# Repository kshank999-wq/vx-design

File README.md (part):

# VX Design

Spec-driven electronics and hardware engineering platform: specification → plan →
sourced parts → power budget → KiCad board → manufacturing files → enclosure, with every
decision traced to evidence.

The master specification is [docs/SPEC.md](docs/SPEC.md) (v1.1). It merges the v0.1 platform spec and the
v1.0 product spec, and marks what is built. The source documents are in [docs/specs/](docs/specs/), and
[docs/ASSESSMENT.md](docs/ASSESSMENT.md) holds the feasibility assessment. Deployment (Vercel, Supabase, worker host):
[docs/DEPLOY.md](docs/DEPLOY.md).

## Layout

| Path | Purpose |
|---|---|
| `apps/web/` | Next.js interface and Vercel endpoints |
| `services/orchestrator/` | Worker lifecycle, planning, approvals, queue |
| `services/engineering/` | KiCad / CAD / simulation adapter workers |
| `packages/contracts/` | Typed task, artifact, evidence and decision schemas |
| `packages/integrations/` | Provider connectors and capability registry |
| `packages/planning/` | Spec ingestion (DOCX/PDF/Markdown), cited requirement extraction, plan generation and validation |
| `supabase/migrations/` | Postgres schema, RLS and policies |
| `supabase/seed.sql` | G0 capability matrix starting rows |
| `tests/fixtures/` | Small circuits, STEP models and golden outputs |
| `docs/` | Assessment, architecture decision records, runbooks |

## Getting started

Requires Node 22+ and pnpm.

```bash
pnpm install
pnpm typecheck
pnpm test
pnpm test:db   # applies migrations to a throwaway local Postgres and runs schema tests
pnpm dev       # web app on http://localhost:3000
```

G0 capability audit (needs Docker): `./scripts/g0-run.sh` builds the engineering worker image,
runs every tool spike and writes [docs/g0/capability-matrix.md](docs/g0/capability-matrix.md).

To connect a Supabase project, copy `.env.example` to `apps/web/.env.local` and fill in the
project URL and anon key, then apply `supabase/migrations/` (Supabase CLI: `supabase db push`).

## G1: specification to approved plan

1. **Upload** a DOCX, PDF, Markdown or text spec. It is parsed into sections and blocks with stable ids (`S2.1.p3`).
2. **Extract requirements.** Claude returns each requirement with a block id and a verbatim excerpt. Every
   excerpt is checked against the document; unverifiable ones get one correction round, then are dropped
   and reported. Codes (`REQ-PWR-002`) are assigned deterministically in document order.
3. **Review**: confirm or reject requirements; ambiguities and open questions are listed.
4. **Generate a plan.** Claude proposes a task graph; deterministic checks require valid keys, known
   dependencies, no cycles, an acceptance test per task, and every requirement covered or explicitly
   deferred (up to 2 repair rounds). High/critical-risk tasks always get an approval gate.
5. **Edit** tasks while the plan is a draft, **submit**, then an owner/reviewer **approves** (or returns it
   with a note). Approval freezes the baseline, supersedes the previous one and makes tasks runnable.
   Changes after that go through **Revise**, which creates a new draft version.

The database enforces the workflow (status changes only through `submit_plan` / `decide_plan` /
`revise_plan`; frozen task definitions; dependency order), covered by `supabase/tests/planning_test.sql`.

Run locally (needs Docker):

```bash
npx supabase start                 # local Postgres/Auth/Storage, applies migrations + seed
cp .env.example apps/web/.env.local   # fill in the local URL/anon key printed above
pnpm --filter @vx/web build && pnpm --filter @vx/web start
pnpm test:e2e                      # browser flow; run the app with VX_LLM=offline to avoid model calls
```

### Guided setup and the look of the app

**Guided setup** (`/projects/<id>/setup`, "Guided setup" on the project page) takes a new project through five steps,
one at a time:
1. **Project:** name, code and description, and the product class chosen from chips.
2. **Mock-up:** reference images, and a link to the concept rounds.
3. **Intake:** markets, power, radios and standards as chips, size as three boxes, and the feasibility check.
4. **Inputs:** specifications uploaded here; parts and prior work are counted.
5. **Review and plan:** what is still missing, then "Generate the plan".

A readiness ring shows how much of what the planner needs is filled in. A manifest and the project's recent activity
sit beside the steps.

**Screens, not long pages:**
- **Project page tabs:** Overview, Documents, Requirements, Plans and runs, Standards and Team (`?tab=`).
  - **Overview:** summary tiles, the Project inputs button and the grouped sections.
  - **Requirements:** 50 per page, with search and status and document filters.
  - **Documents:** the first 8 are shown, with a button for the rest.
- **Project inputs:** five screens (Specifications, Mock-ups, Parts chosen, Prior work, Plan) with the step list on the
  left, Back and Continue, and a summary of what the plan builds on (`?step=`). Forms return to the step they were sent
  from.
- **Long lists:** the earlier-work register's subsystem groups start closed when there are more than 30 items.
- **Plan page:** tasks are grouped by stage (S0–S8). A stage index at the top shows the task count and how many are
  done. Each stage is a collapsible section with its task count, hours, approval gates, high-risk tasks and, once
  approved, a progress bar.
- **Project menu:** on every project page (staff), under the header. It holds Overview, Inputs and Workspace, then
  Define, Design, Make and Prove as drop-downs, with the current page and its group highlighted.
- **Busy pages in tabs** (`SectionTabs`): one section at a time. The open tab comes from `?tab=`, else the last tab opened
  on that page in this browser session (so saving a form returns to it), else where the work is.
  - **Run:** report, tasks, activity. Approvals waiting stay above the tabs.
  - **RFQ:** manifest, files, suppliers, packet, emails, quotes. It opens at the current step.
  - **Flux report:** summary and findings, migration plan, current design, revisions, earlier decisions, files.
  - **Validation:** verification, units, test plan, faults, test runs.
  - **Manufacturing routes:** parts to make, add a part, export for 3D printing.
  - **Release:** readiness, files, issue (draft) or files, changes from the last revision, production lots (issued).
  - **Compliance:** items grouped as failed, open, passed and not applicable; suggestions from the intake; certified modules.
  - **Lifecycle:** watch, cases, cost history. A case is impact, substitutes, resolution, opening at its current step.
  - **Production lot:** units, inspections, disposition.
  - **Intake and risks:** intake, risk register (forms return to their tab).
  - If a tab empties after a form (its last suggestion added), the page shows where the work is.
- **Stages:** one line per stage with its task count and status; the current stage (and any reopened or signed off past
  open items) is expanded.
- **Folder uploads:** every upload box takes files, a whole folder (the "Choose a folder" button) or anything dragged onto
  it, sub-folders included. System clutter (.DS_Store, Thumbs.db, __MACOSX) is left out, and each box keeps only the
  file types it takes, saying how many it left out. Flux imports take whole export folders. When two files share a
  name, the sub-folder becomes part of the name.
- **Updating the plan:** the planner reads every input, including the parts chosen from their datasheets (PT-n, with
  their specifications and model files; every one must be used by a task or its replacement argued). When anything is
  added or changed after a plan is made, the project, Project inputs and plan pages list what is new. "Update plan vN
  with these changes" sends the current plan's tasks and only the new or changed inputs; the planner returns just the
  tasks to add, change or remove, which are merged and checked like a full plan (every requirement covered or deferred,
  every part addressed). The new version says what it changed. "Rebuild from scratch" plans everything again.
- **Plan being built:** a large card at the top of the project, Project inputs and plan pages shows what is happening
  (updating vN or building from scratch), a live clock and the steps, and warns when no worker has picked the request
  up after three minutes. The update buttons are hidden meanwhile.
- **AI usage:** every AI call (website and workers) is priced from one token price table (`packages/planning/src/llm/pricing.ts`)
  and recorded with its purpose, tokens, cache use, time and who asked (`record_ai_call`); calls that fail after the
  model ran are billed and marked. Each project has an **AI usage** page (menu): this month, all time, cost per minute
  of AI time, by activity, and every call. The Account page totals AI spend by month, project and activity.
- **Billing (groundwork):** Account → **Billing** shows the prepaid balance, the plan, card top-ups (Stripe Checkout)
  and a statement per month (page and CSV) listing every charge with the AI call behind it: project, activity, model,
  tokens, our cost and the amount charged. Plans on offer (placeholder prices in `account_plans`): **Pay as you go**
  (no fee, cost + 25%), **Studio** ($50/month, AI at exact cost), **Team** ($150/month including $100 of AI at cost).
  Every cost event in a billed account's projects is charged as it is recorded (`billing_ledger`); the plan fee once a
  calendar month. When the balance reaches zero, AI work pauses (running runs stop at their next checkpoint, plan
  builds and AI actions are refused before any call is made) until credit is added. The internal plans (`standard`,
  `unlimited`) are not billed and keep their monthly allowances. Estimates on billed plans include the markup.
- **Build vs buy** (Define → Build vs buy, and a link on the plan's selection tasks): describe a subsystem (kind,
  interfaces, radios, the supply rail, the space, the markets it must be certified for). Code checks every module in
  the modules catalog against it and says why each one does not fit, or which facts the catalog lacks (unknown, never
  assumed). **Find more modules with AI** asks the model for candidates; only part numbers a distributor (or the parts
  catalog) confirms are added, as draft catalog entries that say where they came from (the model's certification
  claims are kept as a note, not as certifications). **Compare** creates a trade study of up to four fitting modules
  against a custom (chip-down) design on the module-vs-custom criteria: catalog facts where known, stated rules of
  thumb (integration and design hours at $120/h, certification costs, weeks to prototype) where not, all editable;
  **Fill from catalog** adds current prices. A decided study is a decision the next plan update builds on (TS-n).
- **Where things stand, everywhere.** Under the project menu, every project page shows the design run live: what it
  is working on (with a running clock and its latest step), how many results wait for you, the AI spend, and a link
  back to the run; the menu has **Runs** (every run). The run page has a large live panel and **Raise budget** (a run
  stopped only by its budget continues). The Workspace opens with a step-by-step line (inputs, concept, plan, design
  run, your approvals, manufacturer package: done, working, or your turn) and its activity panel with the results
  waiting for approval, what is working now and the recent activity log. With stage gates off, the stage bar follows
  the work.
- **Overnight runs and continuing a run.** "Run straight through (overnight)" (when authorizing, on the run page, or
  when continuing) approves every result whose VX Design checks pass instead of stopping for it; each automatic
  approval is recorded with the reason it would have stopped, on the authority of whoever turned it on. Failed checks
  still stop that task while the rest carries on; releases are never issued automatically. A run that stopped for
  input continues as the same run (**Continue the run**), with a new budget, approving what passed when overnight is on.
- **Plain-language summaries and questions for you.** When a step finishes, a small, inexpensive model writes 2–4
  sentences in everyday language: what was done, what it means for the product, whether the checks passed. The
  summary is shown first on approval cards, finished checklist items, result tiles, the run page and the result page,
  with **See the full technical explanation** one click away. The same pass may raise up to three questions only the
  owner can decide (markets, budget, features), each with a recommendation. Runs never wait on a question: the work
  follows the recommendation until someone answers under **Questions for you** in the Workspace (a choice, their own
  words, the recommendation, or "Not relevant"), and every later step is given the answers. The live strip shows how
  many questions are open; **Questions** (project menu) lists them one card per question, grouped by the step that
  raised them, with the recommendation highlighted and "Accept all recommendations". Each question can be read aloud (🔊) and answered by
  dictation (🎤), using the browser's own speech features (dictation in Chrome, Edge and recent Safari). Cost: part of "Plain-language summaries" on the AI usage page.
- **Calculation checks have roles.** Each check in a calculation is a requirement (must pass), a stretch target
  (reported, does not block) or an information-only scenario (an alternative the design does not rely on, such as an
  oscillator without the compensation the design uses). A scenario counts as information only when a requirement
  check on the same requirement sits beside it, and a stretch check on a must requirement is a requirement, so a
  real shortfall still fails the step.
- **The look, always in view.** Concepts opens on a **Mock-ups** tab (the team's sketches, renders and photos, large)
  under a "What we are building" strip with the frozen design or first mock-up; **Design freeze** and **Generated
  concepts** are tabs beside it. Once a design is frozen, the worker describes its image in words once (a small
  model looking at it) and every later step's context carries the look: that description, the envelope, the finish
  and the list of mock-ups.
- **Import existing designs** (project menu: Design → Import existing designs; was "Flux import"). Each import records
  where the work comes from (KiCad, Eagle/Fusion, Altium, EasyEDA, PADS, CADSTAR, Allegro/OrCAD, Flux, SolidWorks,
  Fusion 360/Onshape/Creo/Inventor, or any other tool), and the page says what to export from each. Running it audits
  the exports as before (BOM, placement, netlists, Gerbers, revisions, earlier decisions) and also sends every native
  board file to the KiCad worker (`import_conversions`): KiCad's own importers convert Eagle, Altium, EasyEDA, PADS,
  CADSTAR, Allegro, P-CAD, Fabmaster and SolidWorks PCB boards to KiCad (`vx_eng import-board`), the design-rule check
  runs, and the board's size, layers, parts and nets are reported with the converted board to download. STEP, IGES and
  STL models are measured (`vx_eng model-facts`). Schematics stay in their original tool (KiCad converts boards only);
  IPC-2581 and ODB++ go through the manufacturing-export audit. SolidWorks' native files need a STEP export.
- **Prices and earnings.** Customers see one price per AI call (our cost times their plan's rate). Plans describe their
  price per million tokens, never the markup; statements, the CSV, the billing summary and the AI usage page carry no
  "our cost", and the database withholds the ledger's cost column and the plans' markup from customers. VX Design
  administrators (`platform_admins`, added by SQL) see our cost, price and markup everywhere, and **Admin → Earnings**:
  markup earned from customers per month, and what in-house (unbilled) projects would have earned at a reference
  markup they set there.
- **Resolving a stopped run.** "What you need to do" shows one card per problem: what went wrong in plain words and
  buttons to **Try again** (that step, and the run continues), **Give guidance** (a box opens under the card; "Save
  guidance and try again" or "Save guidance only"; earlier guidance is listed on the card), **Save for later** (the run
  leaves it alone; **Bring back** under "Saved for later"), and for critical-risk steps **Include it and continue**.
  One **Fix everything above and continue the run** button sits below, with the run's budget shown and changeable under
  Options (every button uses the run's own budget). Older runs say so and link to the latest. When a worker is stopped
  (an update or restart), it hands its steps straight back to the queue instead of letting them count as
  interruptions; steps already blocked by interruptions are put back when the run continues.
- **DigiKey through the website.** When DigiKey's firewall blocks a worker's own connection, set `VX_PARTS_RELAY_URL`
  (the website's `/api/sourcing/digikey`) and `VX_PARTS_RELAY_TOKEN` on the worker, and the same token plus
  `DIGIKEY_CLIENT_ID`/`DIGIKEY_CLIENT_SECRET` on the website: the worker's DigiKey lookups then go through the website. While the website is behind Vercel's own sign-in, also set
  `VX_PARTS_RELAY_BYPASS` on the worker to the project's Protection Bypass for Automation secret.
  Opening `/api/sourcing/digikey` in a browser shows whether DigiKey answers the website and whether its keys and token
  are set (no secrets shown).
- **Intake reflects the project.** Empty intake fields (markets, radios, power, standards, size, use) are filled from the
  owner's answers, the requirements, the design freeze and the description, with a note saying where they came from;
  saving keeps them.
- **Moving on past a step.** A step that could not finish can be **put on hold and moved on**: it counts as done
  without its result (recorded as a warning, audited), the steps after it run, and it is listed under "On hold" with
  **Do it now**. The parts lookup puts itself on hold when every parts service refuses (keys, approvals, plan limits),
  instead of retrying. A step that ran out of its own AI limit gets **Raise it and try again** (a per-step override; the
  approved plan is unchanged). Run pages and the status bar follow the run that is working; a stopped run whose work is
  running in another run says so and links to it. The run page refreshes every 20 seconds.
- **Run chat.** Beside "What you need to do" on a stopped run is a chat with the design agent. Each step listed
  there has **Give guidance**, which opens the chat on that step: what you write is saved with the step (audited) and
  its next attempt reads it as it reads a reviewer's notes. Questions without a step go to the agent as in the
  Workspace. Dictation and read-aloud work here too.
- **Parts services that refuse.** A parts service that rejects the key, has used up its plan, or answers with an
  anti-bot page is asked once per parts list and then skipped with the reason, instead of failing every line.
- **What you need to do.** A stopped run says in plain words what stopped it: steps that could not finish (and why),
  critical-risk steps outside the run (only the owner can include them), results waiting, open questions, and steps
  waiting on hardware. **Fix these and continue the run** retries the failed steps with a fresh retry allowance,
  includes critical-risk steps if the owner ticks it, and can raise the AI and compute budgets. AI answers that run
  past the output limit are retried once with the full 128K output and less reasoning effort; answer formats too large
  for the API's constrained decoding are retried with the format in the instructions and checked here.
- **Approvals for non-engineers.** Each result waiting for approval says in plain language what VX Design checked
  and whether it passed ("Passed: all 4 checks passed"), with the engineering details folded away. **Approve everything
  that passed** approves every waiting result whose checks all passed; anything with a failed check is held.
- **A mock-up is the concept.** On Concepts, a project mock-up (or render, sketch, photo, drawing) can be frozen as the
  industrial design directly, with its envelope, instead of generating concepts (`concept_from_reference`).
- **Cost before you click:** each button that starts AI work shows its likely cost and where the figure comes from:
  plan update and rebuild, plan from requirements, reading specifications (only the blocks rules cannot read are
  counted; "no AI cost" when rules read it all), reading datasheets, chat questions and model comparisons. Figures come
  from this project's recorded calls, else the account's other projects, else typical figures (`apps/web/lib/cost-estimate.ts`).
- **Reading model:** each project chooses the model that reads its specifications and part datasheets (Opus 5.5 by
  default, Sonnet 5.5 or Haiku 5.5): AI usage → "Choose or compare", or the link on the Specifications step. **Compare
  models** reads one specification again with the chosen models, saves nothing as requirements, and matches each
  result against the requirements already read from it (same source paragraph, same meaning): found, missed, extra,
  kind and priority differences, cost and time, with the lists to check. Comparison calls show as "Model comparison".
- **Requirements with less AI:** a block identical to one already read in another specification of the project (a
  new revision) reuses those requirements; a clear sentence with one shall/must/should is read by rules (kind from its
  words, an acceptance criterion from its figures, vague words and TBD marked ambiguous); every other block goes to the
  model, and only those blocks are sent. Nothing is skipped by guesswork: only sections about the document itself
  (revision history, glossary, references, overview). Each specification shows how many requirements came by rules,
  reused, or by AI.
- **Parts from data before AI:** each datasheet's part number is found without AI (a "Part number" or "Ordering code"
  label, or a code in the file or package name that the datasheet itself contains) and looked up in the saved parts
  catalog, then at the distributors configured on the web server (Nexar, DigiKey, Mouser). An exact match supplies the
  maker, description, specifications, package and lifecycle; only datasheets nothing matches are read by AI. The result
  says how many came from data and how many from AI, and each part notes where its specifications came from.
- **Part packages (ZIP):** a manufacturer's ZIP can be dropped on Parts chosen as it is: it is opened, and its datasheets
  and 3D models become part files, noted with the package they came from. A model with no part number inside goes with
  the part its own package describes. ZIPs added on another step are listed on Parts chosen with "Read them as parts".
- **Workspace activity panel:** the plan's tasks are grouped by stage, with done/total. Stages with open work start
  expanded.

**Look:** the clean light design is the template: a blue-grey background with a faint blueprint grid, white cards,
navy panel headers in the workspace, and the S0–S8 stage strip on the project page and the workspace. Dark mode follows
the system until someone picks one with the switch in the header. The logo and favicon come from
`VX Design Chrome Orbit Logo.png`. The setup's chips, readiness ring and cyan accents come from the dark-tech concept.

### Project inputs

**Project inputs** (`/projects/<id>/inputs`, linked first on the project page) is where everything a plan is built
from comes together, and where the plan is generated:

1. **Specifications.**
   - **Upload:** any number at once, one per board, for the enclosure, for the software. Each file goes from the
     browser to a staging folder and is then checked and parsed as before.
   - **Extract:** "Extract requirements from N documents" reads them at the same time, then stores the results one
     document after another, so requirement codes continue across documents.
   - **Duplicates:** requirements that say nearly the same thing in two documents (word overlap ≥ 75%) are listed for
     a person to merge or keep.
2. **Mock-ups and references (`REF-n`).**
   - **What they are:** how the product should look: sketches, renders, photos, dimensioned drawings.
   - **Each one has:** a kind, a title, a note on what it shows and what to keep, and a "use in the plan" switch.
   - **Files accepted:** PNG, JPEG, WebP, GIF and PDF, checked on their bytes. SVG is refused because it can carry
     script.
   - **Concepts:** image references can be given to a concept round. The image model gets them as reference images,
     and their notes go into the brief.
3. **Parts already chosen.** Upload the manufacturer datasheets (PDF, or Word/text) and 3D or CAD files (STEP, STL,
   IGES); nothing has to be typed (`@vx/planning` part-identify.ts).
   - **Datasheets:** each is read for the orderable part number, which is kept only if it appears in the datasheet (a
     listed variant that does is used instead). Also read: the manufacturer, what the part is, its subsystem and up to
     12 key specifications. The part is created, or filled in if already listed, with the file attached. Up to 8 are
     read per press.
   - **Models:** each is attached to the part whose number (or variant) is in its STEP header or product names, or in
     its file name. The longest match wins.
   - **Unplaced files:** a file that cannot be read or matched is listed with the reason, and a person picks the part
     or types the number.
   - **By hand:** a part can still be typed in, from a collapsed form.

   Parts someone has already picked (`public.project_parts`), grouped by subsystem:
   - **Each one has:** part number, manufacturer, what it is for, subsystem, how far it got (candidate, selected,
     designed in, laid out, verified, rejected) and a note. A part number is listed once, ignoring case and punctuation.
   - **Files:** datasheets, 3D models (STEP) and drawings are attached to the part. The kind is worked out from the
     file: STEP is a 3D model, PDF a datasheet.
4. **Prior work.**
   - **Flux audits (`PW-n`).** Finished Flux audits marked for the plan. The planner gets, for each: board size, layers
     and whether it is routed; parts grouped by part number and role; rails and connectors; earlier decisions and
     claimed validations, all marked unverified; open problems and suggested next steps.
   - **Files from other tools or engineers (`REF-n`, kind "Prior design").** A KiCad project, a schematic PDF, a BOM
     spreadsheet, design notes, with a note on where each came from.
   - **What was already done: the earlier-work register (`PR-n`).** "Build the list of earlier work" asks a worker to read
     every earlier design document in full: the documents inside the Flux imports, the prior-design files and the
     parts' datasheets. It lists each part and design decision by subsystem with how far it got (considered, selected,
     designed, laid out, verified, rejected, open), quoting the document it came from. Items not quoted word for word
     are dropped. Parts entered by the owner override what the documents say.
   - **Corrections:** people can correct an item's status, add a note or leave it out. Corrections are kept by item
     across rebuilds.
5. **Other inputs.** The intake, the design freeze, confirmed standards and knowledge sources are shown with links,
   and also go to the planner.
6. **The plan.** "What the planner reads" shows the exact context. "Generate plan from these inputs" builds the plan.
   - **Each task** states its basis: it **reuses** earlier work, **adapts** it, **replaces** it, or **starts fresh**,
     citing the inputs it builds on and saying what remains.
   - **Earlier work must be addressed:** every register item that is selected, designed, laid out or verified must be
     cited by some task. A plan that ignores one is sent back for repair.
   - **Replacing:** a task that replaces earlier work must give its concerns and suggest alternatives.
   - **Validation:** a task citing an input that does not exist, or reusing work without citing any, is sent back for
     repair. Imported work is never treated as verified, so reused work still gets acceptance tests that
     re-establish it.
   - **Display:** the plan page shows each task's basis (with the earlier-work items named, and concerns and
     alternatives for replacements) and the inputs the plan was built on.
   - **Kept through changes:** the basis and the input list are stored with the plan and survive revisions and changes
     made from the workspace chat.

**Large plans go to a worker.** Planning hundreds of requirements takes longer than the hosted web server's 5-minute
request limit. Above 80 active requirements (`VX_WEB_PLAN_MAX_REQUIREMENTS`), "Generate plan" records a plan request
(`public.request_plan`) holding everything the planner reads. A worker then generates the plan with no time limit
and stores it as a draft version, with the same checks as a plan made on the web. Project inputs and the project
page show the request's progress (they refresh themselves), then a link to the plan, or the reason it failed. Only
one plan request runs per project at a time. `services/orchestrator/test/plan-request.test.ts` covers this path.

`supabase/tests/inputs_test.sql` covers the database rules: who may add references, the folder they must be stored
in, duplicates, image-only concept references, and the plan's inputs and basis through revision.
`pnpm test:e2e:inputs` covers the browser flow.

## G2: worker backbone

Approved plans are executed by workers (`services/orchestrator`), separate long-running processes
that are never on Vercel. The web app only authorizes runs and shows their status. Once a run is
authorized, the browser can be closed.

- **Authorize a run** on the approved plan: supervision mode, AI and compute budgets (USD), allowed risk
  levels, retries per task, and optionally stop at the first failure. Pause, resume or cancel it from the
  run page.
- **Durable queue.** Workers claim ready tasks in plan order (`claim_next_task`, `SKIP LOCKED`). Each claim
  is a lease that the worker renews with heartbeats. If a worker stops heartbeating, any other worker
  reclaims its task (`reap_stale_executions`). A task that keeps crashing workers is blocked after three
  interruptions.
- **Checkpoints.** Each executor step's result is saved in the execution's checkpoint. A resumed attempt
  skips finished steps, so model calls are not repeated, and it does not count as a retry.
- **Fenced commits.** Every write names the execution, and the database accepts it only from the worker
  that still holds the lease. A worker that was frozen or partitioned cannot commit after another worker
  has taken over. A unique index also allows at most one committed version per artifact per task.
- **Locks.** A worker must hold the per-artifact write lock (`acquire_artifact_lock`) to register outputs.
- **Budgets.** Model tokens (priced in `services/orchestrator/src/pricing.ts`) and worker time are recorded
  in `cost_events`. Reaching a budget stops the run, and in-flight work yields at its next checkpoint.
- **Sign-off.** Outputs commit when checks pass, unless the plan's approval policy requires sign-off, a test
  needs human review, or a Guided run reaches a design task. Those outputs wait on the run page for
  approve or return-with-note.
- **Report.** When nothing more can run, the worker writes an in-app completion report. It covers outputs,
  checks, recoveries, open approvals, spend, and recommended next steps.

Executors so far:
- **Design briefs** cover architecture, components, thermal, mechanical and documentation tasks (power tasks
  use the power calculator; enclosure tasks the enclosure generator; both below). They are Claude-drafted and checked against the task's requirements and acceptance tests.
- **Simulation tasks** (engineering worker): the model writes the analysis as named quantities (each input with
  its source: requirement, datasheet, upstream task or stated assumption), checks against the requirements, and,
  when a circuit matters, a self-contained ngspice deck with `.meas` statements. Every number is computed by the
  built-in calculator and ngspice, not taken from the model; an analysis that does not compute goes back to the
  model, and a check that computes but fails fails the task with the numbers, for a person to decide. Decks are
  refused if they try anything outside the simulator (`.control`, shell, `.include`).
- **Verification tasks**, two kinds. Before manufacturing: a design review that gathers every upstream task's
  tool checks (ERC, DRC, parity, fit, sourcing, power, simulation; any failure fails the review), then has the
  model read each board's circuit against the requirements and list must-fix / should-fix findings; a person
  signs off every review, in every run mode. After manufacturing (a fab task upstream): a hardware test. Draft
  test procedures for its requirements are added to the Validation page and the task waits for built units; it
  passes once approved procedures have passing runs for all of them (Continue on the run page to check again).
- **Boards.** Schematic, layout and board-power tasks name their circuit board (`tasks.board`; plan fixes infer it
  from upstream work or the key, e.g. `tc-sch-io` → `tc`). A board's tasks build on each other: each schematic task
  starts from the board's design so far and must keep its parts, a board's power tree feeds its schematic, and a
  later layout task takes over the earlier board when the circuit has not changed since (no second layout). One
  manufacturing task packages every board (`fab.<board>/…`) and one sourcing task buys for all of them (refs
  `board/R1`).
- **Manufacturing tasks** by what they produce: fab outputs (Gerbers, pick-and-place, panels) make the fab packages
  (engineering worker); documents (bring-up checklists, factory tests, fixtures) are design briefs; the **RFQ package**
  gathers every committed manufacturing output upstream (each board's fab package, BOMs, CPL, drawings, board and
  enclosure models, test plans, service and compliance documents, reviews) into a **draft release**, with a brief for
  the quote request. A person checks its readiness, issues it on Releases and sends RFQs from the RFQ page.
- **Enclosure before the boards:** an enclosure task with no routed board upstream writes the envelope as a design
  record (sizes, stack-up, bays) for the board tasks to work to; plan fixes make a later enclosure task wait for each
  board's last layout, so the housing is built around the real boards.
- Schematic (G3), simulation, PCB layout (G4) and manufacturing (G4.5) tasks wait for the KiCad engineering worker.
- **No paying for loops.** Every repair loop (plans, briefs, circuits, layouts, power trees, enclosures,
  simulations, assembly instructions) stops early when a round reports exactly the same problems as the round
  before, or returns an output it already returned with the same problems; the reason is recorded. Each task also
  has its own AI spend cap per run (by discipline, e.g. $15 schematic, $20 layout, $6 simulation; a task's
  `cost_budget_usd` overrides it): at the cap the task fails, not retried, for a person to decide.
- **Unchanged work is reused across plan versions.** At approval every task gets a fingerprint over its definition,
  the exact text of its requirements, its board and basis, and its upstream tasks' fingerprints. A task identical to
  one finished in an earlier plan takes over its committed outputs and checks (labelled "Reused from vN … unchanged")
  instead of running; a change anywhere upstream reruns everything below it. Sourcing is reused for 7 days only.
  The plan page marks reused tasks; **Do again** runs a reused task, and the reused work after it, afresh.

```bash
pnpm worker                        # SUPABASE_URL, SUPABASE_SERVICE_ROLE_KEY, ANTHROPIC_API_KEY (or VX_LLM=offline)
pnpm test:worker                   # kills and freezes real worker processes against local Supabase
pnpm test:e2e:g2                   # browser: authorize, close, kill worker, resume, approve, continue, report
```

## G3: first circuit

Schematic tasks run on the **KiCad engineering worker** (`services/engineering/Dockerfile.worker`: KiCad 10 +
the orchestrator + `vx_eng`). Workers advertise the disciplines they can execute, so a worker without KiCad
never claims a schematic task. The run page says when no online worker can run a task. If nothing else can
progress, the run ends with a report saying what it is waiting for.

1. **Design.** Claude proposes a circuit: KiCad library symbols and footprints, nets written as `REF.PIN`, and
   for each part its MPN, manufacturer, datasheet URL and the ratings the design relies on.
2. **Check and repair** (up to 3 repair rounds). `vx_eng` checks the design against the installed KiCad
   libraries:
   - symbols and footprints exist, with close matches suggested when they don't;
   - every pin referenced exists, with the symbol's real pin list in the error;
   - every symbol pin has a pad on its footprint;
   - every pin is connected or explicitly marked unconnected.
   
   It then generates the native schematic and runs KiCad ERC. It also checks that KiCad's own netlist matches
   the design. Every problem goes back to Claude with those library facts.
3. **Component evidence.** Each datasheet is downloaded, and the part number and every claimed rating are
   looked for in its text, with excerpts kept. This is a text match, and the UI says so.
4. **Outputs** (all deterministic, so a resumed task re-uploads identical files):
   - an editable KiCad 10 project (zip);
   - schematic SVG and PDF;
   - the ERC report (JSON);
   - the netlist;
   - a BOM (CSV);
   - the component evidence;
   - the design (JSON).
   
   The web app shows the drawing, the ERC table and the evidence table.

```bash
./services/engineering/build.sh                                        # KiCad engineering image (G0)
docker build -f services/engineering/Dockerfile.worker -t vx-engineering-worker .
pnpm test:eng                       # vx_eng: library checks, deterministic build, ERC negative controls
pnpm test:g3                        # worker routing, schematic build, the stored project re-checked in a fresh KiCad
pnpm test:e2e:g3                    # browser: waits for a KiCad worker, drawing, ERC report, evidence, approve
```

## G4: first board

PCB layout tasks also run on the KiCad engineering worker. They take the **committed circuit design** of their
upstream schematic task, so the schematic must be approved first.

1. **Placement.** Claude proposes:
   - the outline, corner radius and mounting holes (M2, M2.5 or M3);
   - a fab design-rule profile (`jlcpcb-2layer-standard`, `oshpark-2layer`, or `jlcpcb-4layer-standard` for dense
     boards with modules, fine-pitch connectors or more than about 40 parts);
   - a ground pour net, and on 4 layers the inner plane nets (In1 ground, In2 the main supply by default). The planes
     go in before routing, so the router drops those nets to them with vias and routes only signals on the outer
     layers. The fab package checks both inner layers are in the Gerbers and the fab notes give the stackup. When two
     layers leave ten or more connections unrouted, the repair message tells the model to switch to four;
   - a position, rotation and side for every component.
   
   It is given each footprint's courtyard extents from the KiCad library.
2. **Check and repair** (up to 3 repair rounds). Each problem goes back to Claude with exact geometry:
   - `vx_eng` checks the placement with KiCad's own footprints: courtyards must be inside the outline and must
     not overlap on the same side. Through-hole parts and holes block both sides. Problems give the allowed
     position range or the overlap size.
   - It builds a native `.kicad_pcb` linked to the schematic: footprints carry the symbol UUIDs and fields, and
     pads carry KiCad's net names.
   - **Freerouting** routes it. Supply nets get the wider "Power" net class. A ground pour is added on both
     layers.
   - **KiCad DRC** runs with `--schematic-parity` and zone refill. Pads whose thermal spokes can't all reach
     the pour get a solid connection, and DRC runs again.
   - Unrouted connections, DRC errors and parity differences go back to Claude.
3. **3D.** The KiCad library model of each footprint comes from
   [kicad-packages3D](https://gitlab.com/kicad/libraries/kicad-packages3D) at the KiCad version's tag. Models
   are fetched once and cached (`VX_3DMODEL_CACHE`). These are generic package shapes, not manufacturer CAD,
   and the model report says so.
4. **Outputs** (12 per task):
   - the KiCad 10 project (schematic + routed board);
   - 3D renders (iso, top, bottom);
   - copper/silk drawings (SVG, PDF);
   - board STEP and GLB;
   - the DRC report;
   - the 3D model report;
   - the placement.
   
   Routing is not bit-for-bit reproducible, so the files that passed DRC are stashed in storage in the same
   checkpointed step. A resumed task registers those exact files instead of routing again.

The web app shows:
- the 3D render in the approval panel;
- an interactive 3D board (the GLB in `<model-viewer>`);
- the DRC table, split into rule violations, unrouted connections and differences from the schematic;
- the 3D model report and the placement.

Excluded DRC items count as waivers and are reported separately; generated boards have none.

Limits:
- Two-layer, low-speed boards only. Freerouting has no impedance control and no length matching.
- Placement quality depends on the model. The checks guarantee a clean, routed, schematic-matched board, not a
  good one, so review it in KiCad.
- Gerbers, drill, pick-and-place and panelization are in G4.5 (below).

```bash
docker build -f services/engineering/Dockerfile.worker -t vx-engineering-worker .   # now includes the PCB pipeline
pnpm test:eng                       # placement checks, routed fixture board: DRC + parity clean; unrouted and drifted negative controls
pnpm test:g4                        # schematic -> approve -> layout; worker killed after layout; fresh-KiCad DRC/parity/ERC of the stored project
pnpm test:e2e:g4                    # browser: approve schematic, continue, 3D board, DRC report, models, placement, approve
```

## G4.5: fab package

Manufacturing tasks also run on the KiCad engineering worker. They take the **committed routed board** of an
upstream PCB layout task, so the layout must be approved first. No model is involved: every step is
deterministic.

1. **Release gate.** KiCad DRC with schematic parity must be clean on the board being released.
2. **Board-house files.** KiKit writes the package for the board's fab profile (`jlcpcb` or `oshpark`):
   - Gerbers (X2) plus Excellon drill files, plated and non-plated separate, zipped the way the house expects;
   - for JLCPCB, the assembly BOM and pick-and-place (CPL), with KiKit's rotation corrections.
3. **Independent checks.** gerbonara re-reads the Gerbers and drill files without KiCad and checks:
   - required layers and outline size;
   - copper-to-edge clearance against the fab profile;
   - silkscreen inside the board;
   - hole count (plated, non-plated, vias) and the smallest drill.
   
   The CPL is compared with the board's footprint positions and sides, and the BOM with its components.
4. **Package contents:**
   - assembly drawings and a drill map;
   - `FAB-NOTES.txt`, the settings to enter on the order form (size, layers, thickness, copper, finish, mask,
     minimum track and drill, hole counts, missing LCSC numbers);
   - an optional 2x2 KiKit panel with mousebites, rails, tooling holes and fiducials;
   - one zip with a sha256 `manifest.json`.
5. **Release sign-off.** A fab package always waits for approval. The package page lists the ordering steps,
   shows the fab notes and the panel, and has a check page (Gerbers, CPL, parts, manifest). VX Design never
   places orders.

Limits:
- JLCPCB assembly needs an LCSC part number on every line. Until sourcing (M-SRC) fills them in, the package
  says so and only the bare boards can be ordered.
- KiKit's rotation corrections cover common packages; always check the house's placement preview.
- The G4.5 exit test is physical: order the board, assemble it and test it. That needs a real (not offline)
  design.

```bash
docker build -f services/engineering/Dockerfile.worker -t vx-engineering-worker .   # adds gerbonara
pnpm test:eng                       # fab package + negative controls: wrong outline/drills, fab limits, CPL/BOM tampering, DRC gate
pnpm test:g45                       # schematic -> layout -> fab package via the worker; manifest and package re-checked
pnpm test:e2e:g45                   # browser: order card, fab notes, independent checks, panel, approve
```

### Exchange formats (S5)

Every fab package also carries `formats/`:
- **Files.**
  - IPC-2581 revision C (XML).
  - ODB++ (zip).
  - The IPC-D-356 netlist, for bare-board electrical test.
  - A DXF of the board outline in mm, for mechanical and enclosure suppliers.
- **Checks.** KiCad writes them; `vx_eng/exports.py` reads each one back with its own parser and compares it with the
  board as pcbnew reports it:
  - copper and signal layers;
  - every component;
  - every net with two or more pads;
  - the outline size, within 0.15 mm.

  A mismatch fails the package, like a Gerber error does.
- **Reproducible.** The dates KiCad stamps inside IPC-2581 and ODB++ are fixed, and the ODB++ archive is rewritten with
  sorted entries, so the same board gives byte-identical files (checked by the KiCad regression tier).
- **Fab notes.** They say which set to send to whom: Gerber X2 + Excellon as the primary set, IPC-2581 or ODB++ where
  a house prefers one, IPC-D-356 for electrical test, DXF for mechanical work.
- **Storage.** Each file is stored as its own artifact and covered by an "Exchange formats" check on the task.

### Inspection plans (S5)

**Inspection plans** (`/projects/<id>/inspection`) say what to check on bare boards, assembled boards and enclosures.
Each item gives the characteristic, the method, the stage (incoming, in-process or final), the sample
(100%, sample or first article), the acceptance criterion, a reference, and whether it is critical.
- **Drafting.** `packages/planning/src/inspection.ts` builds drafts deterministically:
  - **Board plans** come from the latest committed fab check. They cover outline, thickness (from the fab profile),
    layers, holes and smallest drill, IPC-A-600 workmanship, and electrical test against the IPC-D-356 netlist.
    PCBA plans add:
    - placement;
    - polarity of the polarized parts it names;
    - IPC-A-610 joints;
    - bridges on parts of 0.5 mm pitch or finer;
    - X-ray for QFN, DFN, BGA and other bottom-terminated parts;
    - through-hole fill;
    - bottom-side parts;
    - the approved production test;
    - serial labels.

    DNP parts, mounting holes, fiducials and test points are not counted as components.
  - **Enclosure plans** come from the fit report: overall size, wall, each boss and each opening, material, finish and fit.
    Their tolerance is the loosest one recorded in any supplier's rules for the enclosure's process, with that supplier
    named. Otherwise it is a typical figure, marked as assumed.
  - **Typical figures** that do not come from a supplier say "confirm with the fab".
- **Editing and approval.** Owners and engineers edit drafts: change any field, remove items, add items. The database
  rejects unknown stages and samples, duplicate keys, and empty methods or acceptance criteria. Owners or reviewers
  approve, which freezes the version; a trigger refuses later edits.
- **Revisions.** Revising makes v2 as a new draft. Approving it supersedes the previously approved plan of the same kind.
- **CSV.** Each plan downloads as CSV for the supplier (`…/inspection/<plan>/csv`).
- **Production lots.** A lot names the approved plan it is inspected against, and the lot page lists the plan's checks
  next to the inspection record.

## M-SRC: part sourcing

Sourcing tasks take the **committed circuit design** of the upstream schematic task and produce a sourced BOM.
They run on any worker that has at least one distributor configured. A worker without keys leaves them alone,
and the run page names the keys that are missing.

- **Providers** (`packages/integrations/src/sourcing/`), in fallback order:
  - DigiKey v4 (primary; free API);
  - Mouser v1 (fallback A; free API);
  - Nexar/Octopart (fallback B; billed per part, so asked only for lines the free distributors did not find. Its
    offers include LCSC, which gives the JLCPCB part numbers; without it, lines are flagged "no LCSC" for assembly).
  
  Every configured provider is asked; a failing one is recorded and does not stop the line. Request and
  response field names come from the vendors' own Swagger specs and live GraphQL schema. Contract tests use
  documented response shapes (`packages/integrations/test/fixtures/README.md` gives each fixture's
  provenance), and `pnpm --filter @vx/integrations test:live` checks each provider for real once its keys
  are set.
- **Identity.** Each part number is normalized and the manufacturer name is matched against known aliases.
  Every result is labelled an exact match, a packaging variant (e.g. `…TRG1`) or a different part. When
  providers disagree on lifecycle or manufacturer, the line is flagged.
- **Generic passives** (no MPN in the design) are chosen by rules:
  - the same value and package;
  - a capacitor voltage rating at least twice the rail voltage read from the net name (16 V when the
    rail is unknown);
  - LCSC-available first, then stock, then price.
  
  They are labelled "chosen by rules: review", and up to three alternates are kept.
- **Pricing** at 1, 10, 100 and 1000 boards: the cheapest single offer with enough stock, honouring MOQ,
  multiples and price breaks. Shipping, duty and assembly are not included.
- **Flags**: single source at 100 boards, lifecycle (obsolete, NRND, unknown), no LCSC number, no price, and
  provider errors. A line that cannot be sourced fails the task; nothing is invented.
- **Outputs**: `sourced-bom` (JSON, shown as a table with offers), a CSV and an `lcsc-map`.
  - The fab package writes live LCSC numbers into the schematic and board fields, so JLCPCB's assembly BOM
    is filled in.
  - Fixture numbers are never applied.
- **Catalog.** Live results go into the shared `parts` and `offers` tables, with each offer's observation
  time; fixture results never do. `part_models` is the manufacturer 3D model library (see below).
  Provider calls are metered in `cost_events`.

Not done yet in M-SRC: LCSC/JLCPCB's own APIs (both need an application). The 3D model library is below. The power calculator is below. No live distributor call has been made yet, because there are no keys.

```bash
pnpm --filter @vx/integrations test        # identity, pricing, BOM resolution, adapter contracts (fake HTTP)
pnpm --filter @vx/integrations test:live   # real calls; runs each provider whose keys are set
pnpm test:msrc                             # schematic -> sourcing (fixture worker) + layout -> fab package
pnpm test:e2e:msrc                         # browser: waits for keys, fixture BOM, approve
```

## Power calculator

Power tasks (discipline `power`) run on any worker. Claude proposes the power tree and a deterministic
calculator (`packages/power`) checks it. Calculator errors go back to Claude with the computed numbers, up to 3
repair rounds.

- **Tree.** The tree describes:
  - sources: battery (chemistry, cells, capacity, usable fraction), USB or DC, with their voltage range and
    current limit;
  - converters: LDO, buck, boost, buck-boost or load switch, with rated input range, maximum current,
    quiescent current, dropout or efficiency, θJA, Tj(max), soft-start and an `enable_after` for sequencing;
  - rails with their capacitance;
  - loads, with current per operating mode and a peak;
  - modes, with hours per day;
  - sequencing rules.
  
  Every source, converter and load carries a basis: datasheet, requirement, measurement, calculation or
  assumption.
- **Calculation.** Voltages are worked out top-down and currents bottom-up, for every mode at the
  minimum, nominal and maximum source voltage, plus a worst-case peak.
  - LDO: `Iin = Iout + Iq`, `P = (Vin − Vout)·Iout + Vin·Iq`.
  - Switcher: `Pin = Vout·Iout/η + Vin·Iq`.
  - Load switch: `P = I²·Ron`.
  - Junction temperature: `Tj = Ta(max) + P·θJA`.
  - Battery runtime: per mode and over the daily profile.
  - Also efficiency per mode and inrush (`C·V/t_ss`).
- **Checks:**
  - converter current against its rating (error over 100%, warning over 80%);
  - LDO dropout, buck headroom and boost topology;
  - rated input range;
  - junction temperature (error over Tj(max), warning within 25 °C);
  - source and battery limits;
  - inrush;
  - sequencing that nothing enforces;
  - structural errors (unknown rails, two supplies driving one rail, loops).
  
  Missing data is reported, never silently passed: an assumed efficiency, no θJA, no dropout, no source
  limit.
- **Output.** One `power-budget` artifact holds the tree and the full report. The app shows the tree, the
  findings, battery runtime, the converter and rail tables, efficiency, and the basis of every number.

```bash
pnpm --filter @vx/power test        # calculator against hand calculations and every check
pnpm test:e2e:power                 # browser: power task on a plain worker, report page, approve
```

## 3D model library

Manufacturer STEP models for a project's parts, so boards and enclosures use real geometry instead of
KiCad's generic package shapes. Open it from the project page.

1. **Add.** There are three ways in:
   - an engineer uploads a STEP or ZIP (for example an OEM's CAD under NDA);
   - an engineer gives an https link to one;
   - sourcing registers the CAD that Nexar (Octopart's CAD partners) reports for a sourced part.
   
   Models are private to the project unless marked shared (public manufacturer CAD only).
2. **Check** (KiCad worker, `vx_eng model-check`):
   - it tries all 24 axis-aligned orientations;
   - in each, it cuts the model just above its lowest point to find the terminals, and matches them one
     to one to the footprint's pads;
   - each terminal must land inside its pad and cover at least 15% of it, which rejects a model lying on
     its side;
   - it writes an aligned STEP (footprint origin, seating plane at Z = 0, so KiCad needs no transform) and
     a top-view overlay;
   - it measures the body and compares the height with the datasheet value when one is given.
   
   A symmetric terminal pattern is flagged, because pin 1 or polarity then has to be read from the body
   marking. A file that is not a STEP, or a model that does not fit, fails with the reason.
3. **Verify.** A person looks at the overlay and verifies or rejects the model. An inconclusive check, such
   as a QFN whose terminals and body meet at the bottom, needs a note saying what was confirmed by eye.
4. **Use.** Layouts use verified models for parts with a matching MPN, manufacturer and footprint. Each
   model is copied into the KiCad project (`3dmodels/`, referenced with `${KIPRJMOD}`), so the downloaded
   project shows it. It also appears in the board STEP/GLB, and the 3D model check names which parts have
   manufacturer CAD.

The alignment convention is tested end to end: an aligned model is placed on a board in KiCad, the board is
exported to STEP, and every foot is found on its pad.

```bash
pnpm test:eng              # model check: re-oriented vendor model, ZIP, wrong part/footprint/height, pin-1 symmetry, KiCad round trip
pnpm test:models           # upload -> worker check -> verify -> layout ships the model; a non-STEP URL fails cleanly
pnpm test:e2e:models       # browser: upload, overlay, verify
```

## Manufacturing routes and the 3D-printing export

**Manufacturing routes** (`/projects/<id>/manufacturing`, staff only) record, for each physical part, how it is made
now and how it will be made in production (`public.part_routes`).
- **Parts:** the newest enclosure base and lid from each enclosure task, 3D models uploaded on this page (STL or STEP,
  stored as references of kind "3D model"), and parts without a model yet.
- **Each route has:** what the part must survive (outdoors or sun, drops, snap fits, client-facing finish, tight fits,
  rubber-like, clear, hottest temperature), the production process, material and yearly volume, the prototype
  material and quantity, colour and finish, and notes. The needs are pre-filled from the requirements.
- **Suggestions** (`suggestPrototypes` in `@vx/dfm`): prototype options across FDM, SLA, SLS/MJF, urethane casting and
  CNC. Options that cannot meet a need are left out: too little heat resistance, rigid for a rubber part, opaque for a
  window. The rest are ranked on the part's needs, on how well they stand in for the production material, and on
  cost and speed for the quantity. Each suggestion gives its reasons and what to watch out for. Ratings are
  qualitative and heat figures approximate.
- **Per part:** size and volume read from the STL, a material estimate in grams, a warning when it is too big for a
  typical machine, starting print or order settings, and a warning when the prototype material differs from production
  (fit and form only, no strength or drop sign-off).
- **Export for 3D printing:** a ZIP with one folder per part (STL and STEP), `PRINT-SHEET.md` (material, settings,
  quantity, finish, size, estimate, what the print stands in for) and `parts.csv` for a print service's order form.
- **Planning:** the routes go into the planner's context, which is told to design each part for its production process
  and plan the prototype builds and production tooling. The enclosure designer prototypes with the route's process and
  material, and keeps walls uniform when production is injection molding.

## Injection molding package

For a part whose production route is injection molding, **Manufacturing routes** adds a molding section
(`@vx/dfm` molding.ts, `part_routes.molding`).
- **Rules per material** (PC/ABS, ABS, PC, ASA, glass-filled PA66, PP, POM, TPE, acrylic): wall range, minimum draft,
  shrinkage, rib ratio and a clamp pressure factor. Textured mold finishes add draft (e.g. MT-11010 adds 1.5°). These
  are typical design-guide values; the grade's datasheet and the mold maker's DFM review decide.
- **Design check of the STL:**
  - **Draft:** surface nearly parallel to the pull with less than the required draft, and with none.
  - **Undercuts:** surface a straight pull cannot release (a ray in the pull direction hits the part).
  - **Walls:** rays from the surface inward, area-weighted, giving the nominal wall, thin and thick shares and how
    much the walls vary.
  - **Size:** projected area, a clamp force estimate (20% margin) and the shot weight.
  - Large meshes are sampled. Rays from the ends of walls run along the wall, so a few percent of thick readings are
    normal; thick areas are flagged above 5%.
- **Spec:** pull direction, mold finish, material grade, flammability, cosmetic surfaces, tolerances, critical
  dimensions, gate and ejector-mark notes, inserts, cavities and notes.
- **Tool suggestion:** an SPI class and a cavity count from the yearly volume over three years.
- **"Download the mold maker's package":** a ZIP with the part's STEP and STL, `MOLDING-SPEC.md` (the spec, the design
  check, the suggested tool and what to quote: tool, part price at three volumes, DFM report before steel is cut, T1
  samples with a dimensional report, tool ownership), `design-check.csv` and `critical-dimensions.txt`.

**Draft in the generated enclosure.** When the enclosure base or lid has an injection molding route (by the part it
points at, or named "Enclosure base" / "Enclosure lid"), the enclosure task builds it with draft. The worker sets at
least the material's minimum plus what the mold finish needs, whatever the model chose, and records it in the design.
- **Walls:** they flare toward the split, so the base and the lid each release from their mold. The inside is never
  narrower than the straight cavity, so the fit checks still hold.
- **Bosses:** they taper toward their open end. The insert holes stay straight.
- **Lid joint:** the lid locates with the standard molded joint. Its lip is the inner part of the lid wall continued
  below the split, and the base wall is stepped to take it. An inward lip would trap the core. This joint needs a wall
  of at least 1.8 mm.
- **Prints:** printed enclosures keep straight walls and the inward lip, now joined to the lid by a ledge (before, the
  lip was a separate piece).
- **Geometry check:** every join is checked for lost or unjoined geometry, and the lid and base must reach their full
  height.

## Assembly instructions

**Assembly instructions** (`/projects/<id>/assembly`) are the work instructions for building the finished product
(`public.assembly_instructions`, `@vx/planning` assembly.ts).
- **Drafting:** Claude drafts them from the bought parts (Project inputs), the made parts (manufacturing routes), the
  boards (committed layouts, or the Flux imports used for the plan), the enclosure design, and the relevant
  requirements. The engineer can add guidance.
- **Each step has:** parts, fasteners with a torque in N·m (or the reason there is none, e.g. heat-set inserts or
  clips), tools, one action per line, cautions (ESD, battery, cable routing, cosmetic surfaces), a check, an optional
  figure (a project image by its REF code) and a time estimate.
- **Checks:** every made part, bought part and board must be fitted in some step; figures must exist; every fastener
  needs a torque or a reason. Failing drafts go back for repair (2 rounds). Anything still failing is shown, and "Check
  again" re-runs the checks after edits.
- **Versions:** each draft is a numbered version. Engineers edit a draft step by step (move, add, delete). The owner
  or a reviewer approves it, which locks it and supersedes the earlier approved version. "Start a revision" copies a
  version into a new draft.
- **Exports:** "Printable instructions" opens a standalone document to print or save as PDF; drafts are marked as not
  approved. "Download for the assembler" gives a ZIP with that document, its figures, `steps.csv` and `bom.csv`
  (parts and fasteners per unit).

## M-ENC: enclosure and fit

Enclosure tasks (discipline `enclosure`) run on the KiCad engineering worker. They take the **committed
routed board** of an upstream PCB layout task. Claude chooses the housing; `vx_eng enclosure` builds and
checks it, and problems go back to Claude, up to 3 repair rounds.

- **Board facts.** KiCad exports the board and every component as separate STEP solids (drill origin), so a
  collision always names the part. Claude sees each part's height above the board, how far it reaches below
  the board, and its distance to the nearest edge.
- **Design.** Claude sets:
  - the process (FDM, SLA, SLS or CNC aluminium) and material;
  - the wall thickness;
  - the board-edge gap and top clearance;
  - the standoff height;
  - the fastening (heat-set insert, thread-forming screw, or tapped hole);
  - the openings: edge openings through the nearest or a named wall for connectors, and top openings
    (windows, round light or button holes) through the lid.
- **Geometry** (CadQuery). The cavity is the board's own outline offset by the edge gap. The base has a floor,
  walls up to a split plane 2.5 mm above the board, and a standoff with a fastener hole under every mounting
  hole. The lid has walls, a top and a locating lip. Both parts are built additively, because OCCT's
  through-cuts failed silently in testing. Every opening cut is verified to have removed material.
- **Checks:**
  - every component and the board against base and lid, where any overlap is an error naming the part;
  - clearance to the housing;
  - edge connectors set too far behind the wall;
  - parts without a 3D model, reported as unchecked;
  - wall thickness against the process minimum;
  - a fastening the process supports, and a standoff deep enough for it;
  - CNC inner corner radius;
  - build volume.
- **Outputs:**
  - base and lid as STEP and STL;
  - an assembly STEP;
  - an exploded GLB (board in the base, lid beside it) shown in the app;
  - top and front drawings (SVG);
  - the fit report with dimensions, Z levels, standoffs, openings, clearances and estimated mass;
  - the design.

The exit test is physical: print the housing and fit the real, assembled board.

```bash
pnpm test:eng                  # enclosure: fits; lid too low and short standoffs collide (named parts); process rules; edge recess; split planes
pnpm test:enclosure            # schematic -> layout -> enclosure with real KiCad 3D models; STEP re-read as one valid solid
pnpm test:e2e:enclosure        # browser: fit report, exploded 3D view, approve
```

## M-UI: client workspace

Clients get their own login and a workspace per project: a running **chat** on the left, the **results** in the
centre, and the live **checklist** on the right that stops at approval points.

- **People.** Owners invite by email on the project page (client, reviewer, engineer or viewer). If the address has no
  account yet the invitation waits, and it becomes a membership when that person signs up. VX Design does not send
  email yet: share the sign-up link yourself.
- **What clients see.** Requirements, the plan's tasks and their status, approval stops, outputs and their checks, the
  model library and the chat. Runs, executions, costs, the audit trail and worker logs are staff-only, enforced by
  row-level security, not just hidden in the UI. Clients opening the project page are sent to the workspace.
- **Checklist.** The approved plan in order: done, working, queued, blocked, and **approval needed**. At a stop the
  reason is shown with Approve / Return (a note is required to return). Clients, owners and reviewers can decide.
  The checklist refreshes while work is running.
- **Centre.** An overview (progress and one result tile per task) or any output, shown in the same viewers as the
  engineering pages (power report, schematic, 3D board, fit report, BOM, fab package).
- **Chat.** Claude answers from the project's requirements, plan, approvals, outputs, checks and recent chat, read with
  the asker's own permissions. It links the outputs it mentions (they open in the centre) and restates requested changes
  as suggested requirement changes for the team; it cannot approve or change anything. Messages are stored per project
  and every member sees the same conversation. With `VX_LLM=offline` it gives a labelled status summary instead (not AI).
- **Streaming.**
  - Replies appear as they are written: the reply text is read from the model's structured output while it is still
    arriving.
  - The page then shows the stored, signed exchange, so the streamed copy is never the record.
  - Without JavaScript the form posts as before.
- **Plan changes from chat.**
  - **Proposing.** When asked to add, change or remove a task, the assistant proposes that one change; the offline
    stand-in understands "add a task: … after <key>" and "remove task <key>".
  - **Drafting.** Owners and engineers press **Draft this plan change**. That makes a new draft plan version: a copy
    of the newest plan with the change applied, keeping dependency order. Added tasks require approval of their result.
  - **Approval.** The draft is reviewed and approved like any plan; the running plan is not touched. Clients see the
    proposal but cannot draft it.

```bash
./scripts/test-db.sh           # workspace_test: invitations, client visibility, who can decide, chat writes
pnpm test:e2e:workspace        # browser: invite, client signs up, checklist stop, streamed chat, viewer, client approves, plan change from chat
```

Screenshots: `docs/workspace/screens`.

## M-KB: knowledge base

A shared library of standards, regulations, datasheets and application notes, plus each project's own sources.
Every result carries its official link, edition, licence and whether a person has checked it (**Knowledge** in the
top bar).

- **Licensing rules, enforced in the database** (spec §8: a URL is not permission to copy):

  | Licence | Excerpts indexed | File kept |
  |---|---|---|
  | Public domain (e.g. US federal regulations) | yes | yes |
  | Open licence (CC BY, EU legal texts) | yes | yes |
  | Manufacturer document (datasheets, app notes) | yes | no: it stays on the vendor's site |
  | Reference only (IPC, IEC, ISO standards) | no: metadata and official link only | no |
  | Licensed copy | yes, for one project only | yes, in that project's storage |
  | Unknown | treated as reference only | no |

  Moving a source to a licence that allows less deletes the excerpts and stored copy it no longer allows.
- **Standards registry.** Seeded with the spec's starting references (IPC, IEC, UL, UN 38.3, FCC Part 15, EU
  directives, ISO, ASME, Bluetooth, IEEE, USB). Editions are left unconfirmed until a knowledge editor checks
  them with the issuing body. Being in the registry is not proof of applicability.
- **Per-project applicability.** On the project page, engineers propose which standards apply (applies, may apply,
  does not apply) with a reason; an owner or reviewer confirms. Changing an entry needs confirming again.
- **Project sources.** Datasheets, licensed standards and NDA documents added on the project page stay private
  to that project. They are searched only within it, even for someone who belongs to several projects.
- **Search.** Postgres full-text search over the excerpts (any word matches; passages matching every word rank
  higher), plus identifier matching ("ipc 2152" finds IPC-2152). Results show the citation locator
  (section and page), the matched words and the flags. Search runs with the user's own permissions.
- **Curation.** Knowledge editors (granted by the operator: insert the user's id into `knowledge_editors` with
  the service role) add to the shared library, verify sources and review standard editions. Project owners and
  engineers manage project sources; owners and reviewers verify them.
- **Chat.** The workspace assistant searches the knowledge base for each question and cites what it used. It
  gets the project's standards list too, and says when an edition is unconfirmed or only the reference is held.
- **Not yet:** vector (semantic) search, which needs an embedding provider; fetching documents from their URL;
  OCR for scanned PDFs; design tasks citing standards in their outputs.

```bash
./scripts/test-db.sh           # kb_test: licensing rules, write access, project scoping, search, standards review, applicability
pnpm --filter @vx/planning test  # excerpt chunking (section-bounded, page ranges, size limit)
pnpm test:e2e:knowledge        # browser: registry search, add/verify sources, licensed copy isolation, chat citations, licence downgrade
```

Screenshots: `docs/knowledge/screens`. The test documents in `tests/fixtures/kb` are original text.

**Fetching from the official link.**
- **When it applies.** A source's **Fetch from the official link** (or "Fetch the document now" when adding it) reads
  the document at its link, only when the licence allows excerpts.
- **Safety.** The fetch is guarded against reaching inside the network: https only, every resolved address checked at
  connect time (private, loopback, link-local and metadata ranges refused), redirects re-checked, 20 MB and 20 s
  limits.
- **Web pages.** HTML is read for its main content (headings, paragraphs, lists, tables; no scripts, navigation or
  footers) and never stored. PDFs and documents get the upload check, and a copy is kept only where the licence
  allows.
- **Change checks.** **Check the official link for changes** compares the content's sha256. Unchanged content only
  records the check; changed content is re-indexed, and a verified source returns to draft with a note to check the
  edition.

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
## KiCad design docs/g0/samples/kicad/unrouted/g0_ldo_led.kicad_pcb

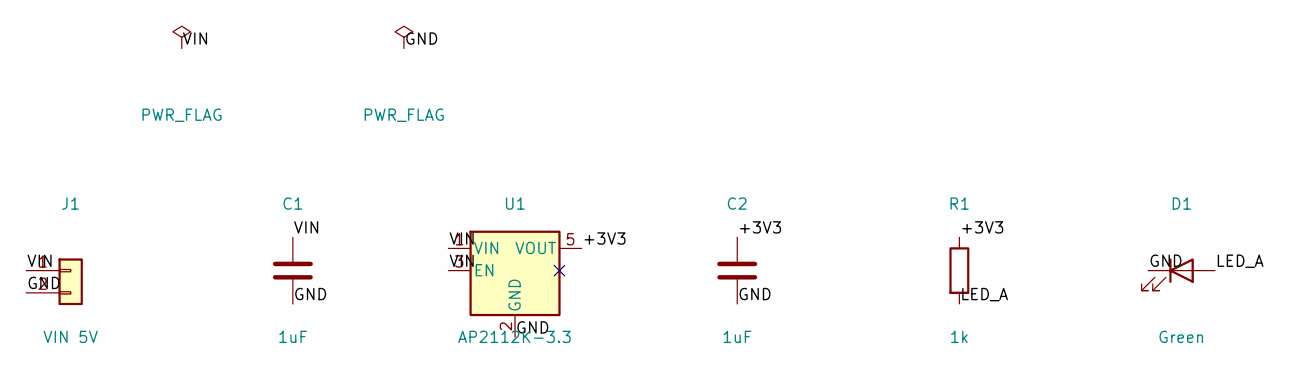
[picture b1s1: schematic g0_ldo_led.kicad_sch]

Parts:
C1, C2: 1uF; C_0603_1608Metric
D1: Green; LED_0603_1608Metric
J1: VIN 5V; PinHeader_1x02_P2.54mm_Vertical
R1: 1k; R_0603_1608Metric
U1: AP2112K-3.3; SOT-23-5

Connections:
/+3V3: C2.1, R1.1, U1.5 (VOUT)
/GND: C1.2, C2.2, D1.1 (K), J1.2, U1.2 (GND)
/LED_A: D1.2 (A), R1.2
/VIN: C1.1, J1.1, U1.1 (VIN), U1.3 (EN)

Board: 2 copper layers, 6 parts (0 on the bottom side), 4 nets, no tracks yet.

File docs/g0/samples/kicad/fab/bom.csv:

"Refs","Value","Footprint","Qty","DNP"
"C1","1uF","Capacitor_SMD:C_0603_1608Metric","1",""
"C2","1uF","Capacitor_SMD:C_0603_1608Metric","1",""
"D1","Green","LED_SMD:LED_0603_1608Metric","1",""
"J1","VIN 5V","Connector_PinHeader_2.54mm:PinHeader_1x02_P2.54mm_Vertical","1",""
"R1","1k","Resistor_SMD:R_0603_1608Metric","1",""
"U1","AP2112K-3.3","Package_TO_SOT_SMD:SOT-23-5","1",""

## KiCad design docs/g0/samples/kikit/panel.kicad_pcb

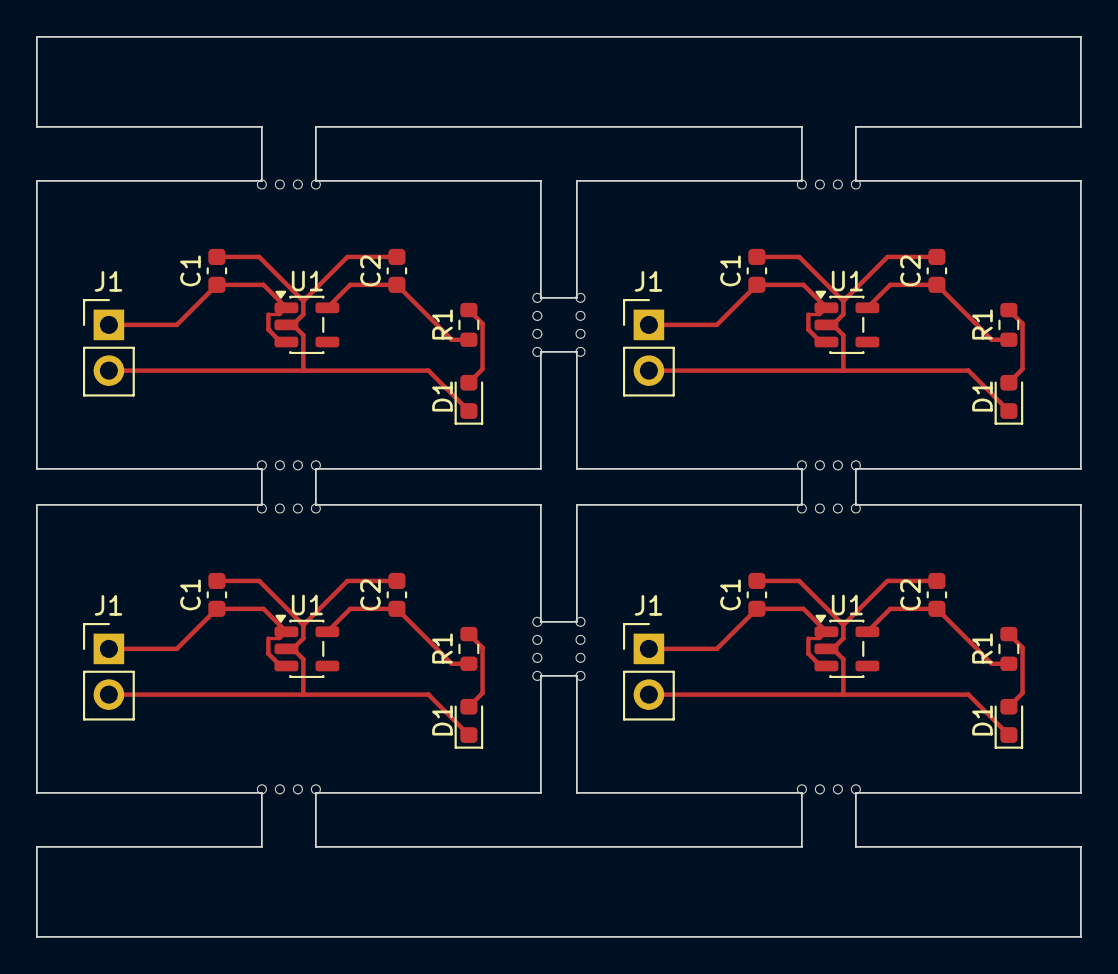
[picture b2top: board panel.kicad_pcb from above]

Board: 2 copper layers, 58.0 x 50.0 mm, 72 parts (0 on the bottom side), 16 nets.

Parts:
C1, C1#2, C1#3, C1#4, C2, C2#2, C2#3, C2#4: 1uF; C_0603_1608Metric
D1, D1#2, D1#3, D1#4: Green; LED_0603_1608Metric
J1, J1#2, J1#3, J1#4: VIN 5V; PinHeader_1x02_P2.54mm_Vertical
KiKit_MB_1_1, KiKit_MB_1_2, KiKit_MB_1_3, KiKit_MB_1_4, KiKit_MB_2_1, KiKit_MB_2_2, KiKit_MB_2_3, KiKit_MB_2_4, KiKit_MB_3_1, KiKit_MB_3_2, KiKit_MB_3_3, KiKit_MB_3_4, KiKit_MB_4_1, KiKit_MB_4_2, KiKit_MB_4_3, KiKit_MB_4_4, KiKit_MB_5_1, KiKit_MB_5_2, KiKit_MB_5_3, KiKit_MB_5_4, KiKit_MB_6_1, KiKit_MB_6_2, KiKit_MB_6_3, KiKit_MB_6_4, KiKit_MB_7_1, KiKit_MB_7_2, KiKit_MB_7_3, KiKit_MB_7_4, KiKit_MB_8_1, KiKit_MB_8_2, KiKit_MB_8_3, KiKit_MB_8_4, KiKit_MB_9_1, KiKit_MB_9_2, KiKit_MB_9_3, KiKit_MB_9_4, KiKit_MB_10_1, KiKit_MB_10_2, KiKit_MB_10_3, KiKit_MB_10_4, KiKit_MB_11_1, KiKit_MB_11_2, KiKit_MB_11_3, KiKit_MB_11_4, KiKit_MB_12_1, KiKit_MB_12_2, KiKit_MB_12_3, KiKit_MB_12_4: NPTH
R1, R1#2, R1#3, R1#4: 1k; R_0603_1608Metric
U1, U1#2, U1#3, U1#4: AP2112K-3.3; SOT-23-5

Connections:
Board_0-/+3V3: C2.1, R1.1, U1#3.5
Board_0-/GND: C1#2.2, C2.2, D1.1, J1#3.2, U1#3.2
Board_0-/LED_A: D1.2, R1.2
Board_0-/VIN: C1#2.1, J1#3.1, U1#3.1, U1#3.3
Board_1-/+3V3: C2#3.1, R1#3.1, U1#4.5
Board_1-/GND: C1#3.2, C2#3.2, D1#2.1, J1#4.2, U1#4.2
Board_1-/LED_A: D1#2.2, R1#3.2
Board_1-/VIN: C1#3.1, J1#4.1, U1#4.1, U1#4.3
Board_2-/+3V3: C2#4.1, R1#2.1, U1#2.5
Board_2-/GND: C1.2, C2#4.2, D1#4.1, J1#2.2, U1#2.2
Board_2-/LED_A: D1#4.2, R1#2.2
Board_2-/VIN: C1.1, J1#2.1, U1#2.1, U1#2.3
Board_3-/+3V3: C2#2.1, R1#4.1, U1.5
Board_3-/GND: C1#4.2, C2#2.2, D1#3.1, J1.2, U1.2
Board_3-/LED_A: D1#3.2, R1#4.2
Board_3-/VIN: C1#4.1, J1.1, U1.1, U1.3

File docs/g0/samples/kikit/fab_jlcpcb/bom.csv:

Comment,Designator,Footprint,LCSC
VIN 5V,J1,Connector_PinHeader_2.54mm:PinHeader_1x02_P2.54mm_Vertical,
1uF,"C1,C2",Capacitor_SMD:C_0603_1608Metric,
AP2112K-3.3,U1,Package_TO_SOT_SMD:SOT-23-5,
1k,R1,Resistor_SMD:R_0603_1608Metric,
Green,D1,LED_SMD:LED_0603_1608Metric,
